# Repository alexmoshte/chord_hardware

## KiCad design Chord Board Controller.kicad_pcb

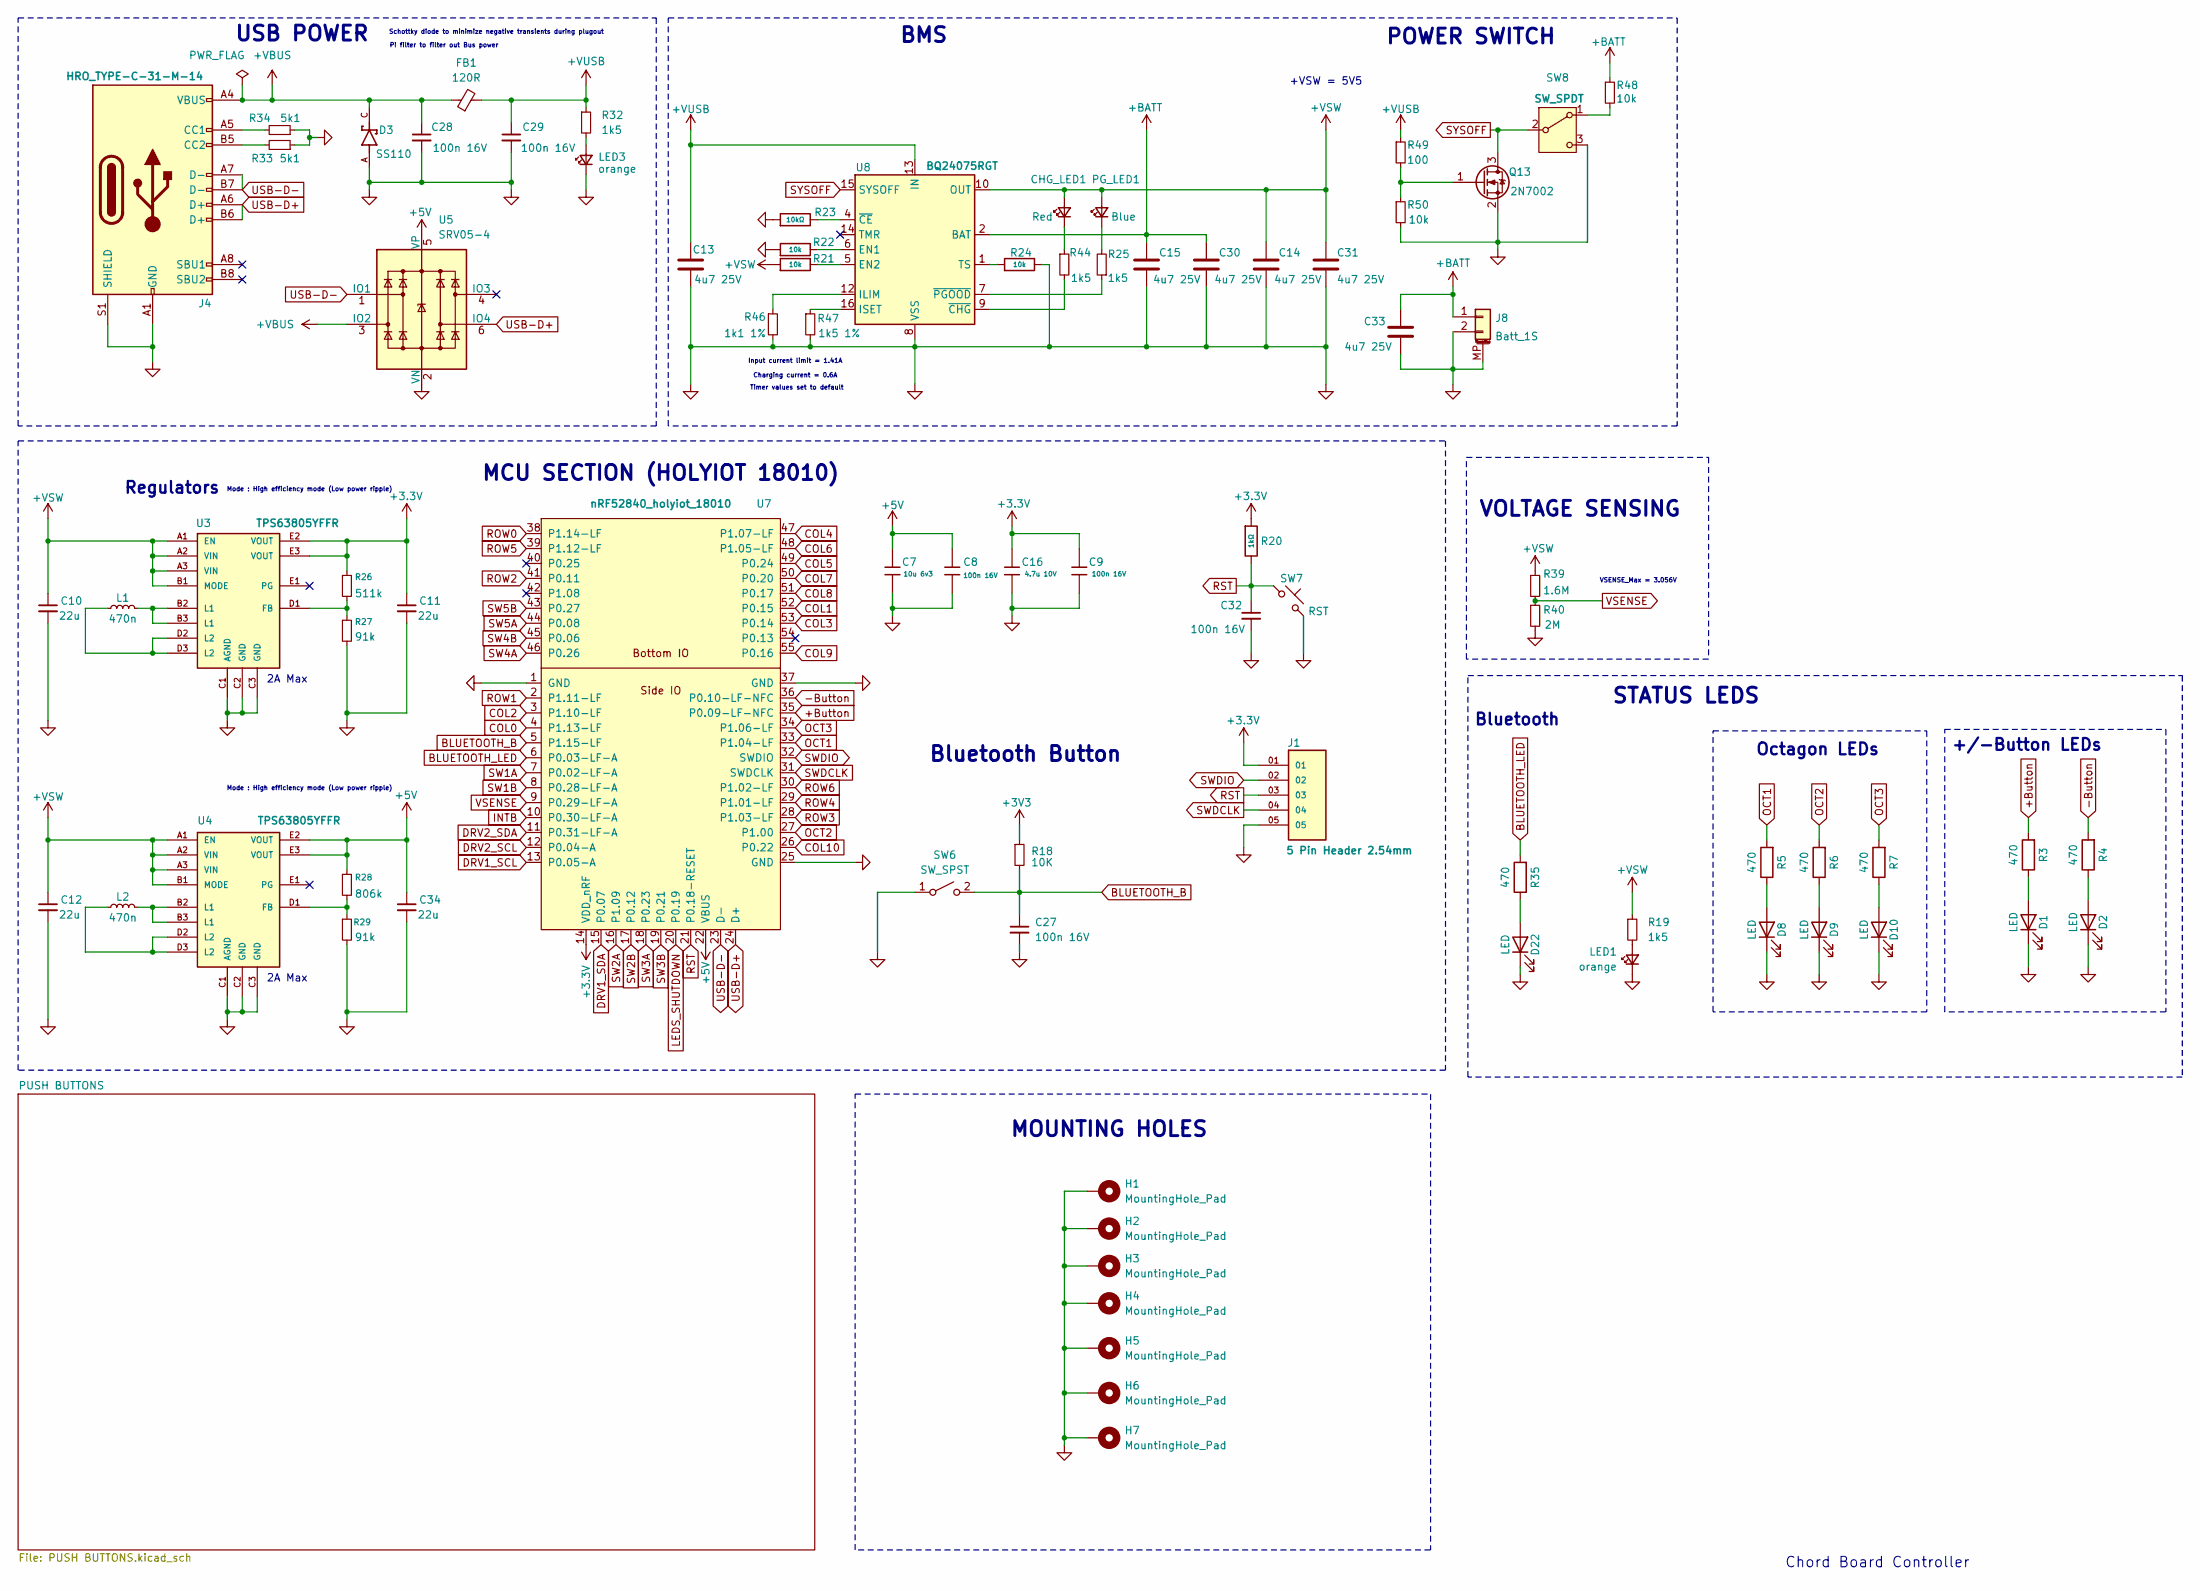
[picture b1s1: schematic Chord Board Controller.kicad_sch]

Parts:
C7: 10u 6v3; C_0402; Voltage Rated 6.3V; Tolerance ±20%; Part CL05A106MQ5NUNC; LCSC C15525
C8, C9: 100n 16V; C_0402; Voltage Rated 16V; Tolerance ±10%; Part CL05B104KO5NNNC; LCSC C1525
C10, C11, C12, C34: 22u; C_0603
C13, C14, C15, C30, C31, C33: 4u7 25V; C_0603
C16: 4.7u 10V; C_0402; Voltage Rated 10V; Tolerance ±20%; Part CL05A475MP5NRNC; LCSC C23733
C27, C32: 100n 16V; C_0402; Manufacturer Part # GCM155R71H104KE02J; LCSC C2649549
C28: 100n 16V; C_0603
C29: 100n 16V; R_0603
CHG_LED1: Red; LED_D1.8mm_W1.8mm_H2.4mm_Horizontal_O6.35mm_Z8.2mm
D1, D2, D8, D9, D10: LED; LED_0603_1608Metric
D3: SS110; DIOM4325X250N; PARTREV O2102
D22: LED; LED_D1.8mm_W1.8mm_H2.4mm_Horizontal_O6.35mm_Z8.2mm
FB1: 120R; FB_0603
H1, H2, H3, H4, H5, H6, H7: MountingHole_Pad; MountingHole_2.2mm_M2; MFR.Part # DNP; JLCPCB part# DNP
J1: 5 Pin Header 2.54mm; PARTREV R
J4: HRO_TYPE-C-31-M-14; USB_C_Receptacle_HRO_TYPE-C-31-M-14; MFR.Part # TYPE-C-31-M-12; JLCPCB part# C165948
J8: Batt_1S; JST_PH_S2B-PH-K_1x02_P2.00mm_Horizontal; LCSC C505023
L1, L2: 470n; L_0402
LED1, LED3: orange; LED_D1.8mm_W1.8mm_H2.4mm_Horizontal_O6.35mm_Z8.2mm
PG_LED1: Blue; LED_0603
Q13: 2N7002; SOT-23
R3, R4, R5, R6, R7: 470; R_0402
R18: 10K; R_0402; Manufacturer Part # CRCW040210K0FKED; LCSC C71617
R19, R32: 1k5; R_0402; MFR.Part # 0402WGF1501TCE; JLCPCB part# C25867
R20: 1kΩ; R_0402; Overload Voltage (Max) 50V; Tolerance ±1%; Part 0402WGF1001TCE; LCSC C11702
R21, R22, R24: 10k; R_0402; Overload Voltage (Max) 50V; Tolerance ±1%; Part 0402WGF1002TCE; LCSC C25744
R23: 10kΩ; R_0402; Overload Voltage (Max) 50V; Tolerance ±1%; Part 0402WGF1002TCE; LCSC C25744
R25, R44: 1k5; R_0603
R26: 511k; R_0603
R27, R29: 91k; R_0603
R28: 806k; R_0603
R33, R34: 5k1; R_0402; MFR.Part # 0402WGF5101TCE; JLCPCB part# C25905
R35: 470; R_0603
R39: 1.6M; R_0402; MFR.Part # 0402WGF8063TCE; JLCPCB part# C29263
R40: 2M; R_0402; MFR.Part # 0402WGF2004TCE; JLCPCB part# C11512
R46: 1k1 1%; R_0603
R47: 1k5 1%; R_0603
R48, R50: 10k; R_0603
R49: 100; R_0603
SW6: SW_SPST; SW_Tactile_SPST_Angled_PTS645Vx31-2LFS; Manufacturer Part # DTSA-61K-V; LCSC C483771
SW7: RST; SW_SPST_SKQG_WithStem; MFR.Part # FRC0402F1101TS; JLCPCB part# C2909306
SW8: SW_SPDT; SW_MSK12C02-HB
U3, U4: TPS63805YFFR; BGA15N40P5X3_225X134X62N; PARTREV A
U5: SRV05-4; SOT-23-6; MFR.Part # SRV05-4-P-T7; JLCPCB part# C179173
U7: nRF52840_holyiot_18010
U8: BQ24075RGT; VQFN-16-1EP_3x3mm_P0.5mm_EP1.6x1.6mm

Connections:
+3.3V: C9.1, C11.1, C16.1, J1.01, R20.1, R26.1, U3.E2 (VOUT), U3.E3 (VOUT), U7.14 (VDD_nRF); also elsewhere on the board
+3V3: R18.1
+5V: C7.1, C8.1, C34.1, R28.1, U4.E2 (VOUT), U4.E3 (VOUT), U5.5 (VP), U7.22 (VBUS)
+BATT: C15.1, C30.1, C33.1, J8.1, R48.1, U8.2 (BAT), U8.3 (BAT)
+Button: R3.2, U7.35 (P0.09-LF-NFC)
+VBUS: C28.1, D3.C, FB1.1, J4.A4 (VBUS), J4.A9 (VBUS), J4.B4 (VBUS), J4.B9 (VBUS), U5.3 (IO2)
+VSW: C10.1, C12.1, C14.1, C31.1, CHG_LED1.2 (A), PG_LED1.2 (A), R19.1, R21.1, R39.1, U3.A1 (EN), U3.A2 (VIN), U3.A3 (VIN), U3.B1 (MODE), U4.A1 (EN), U4.A2 (VIN), U4.A3 (VIN), U4.B1 (MODE), U8.10 (OUT), U8.11 (OUT); also elsewhere on the board
+VUSB: C13.1, C29.1, FB1.2, R32.1, R49.1, U8.13 (IN)
-Button: R4.2, U7.36 (P0.10-LF-NFC)
BLUETOOTH_B: C27.1, R18.2, SW6.2 (B), U7.5 (P1.15-LF)
BLUETOOTH_LED: R35.2, U7.6 (P0.03-LF-A)
COL0: U7.4 (P1.13-LF); also elsewhere on the board
COL1: U7.52 (P0.15); also elsewhere on the board
COL2: U7.3 (P1.10-LF); also elsewhere on the board
COL3: U7.53 (P0.14); also elsewhere on the board
COL4: U7.47 (P1.07-LF); also elsewhere on the board
COL5: U7.49 (P0.24); also elsewhere on the board
COL6: U7.48 (P1.05-LF); also elsewhere on the board
COL7: U7.50 (P0.20); also elsewhere on the board
COL8: U7.51 (P0.17); also elsewhere on the board
COL9: U7.55 (P0.16); also elsewhere on the board
COL10: U7.26 (P0.22); also elsewhere on the board
DRV1_SCL: U7.13 (P0.05-A); also elsewhere on the board
DRV1_SDA: U7.15 (P0.07); also elsewhere on the board
DRV2_SCL: U7.12 (P0.04-A); also elsewhere on the board
DRV2_SDA: U7.11 (P0.31-LF-A); also elsewhere on the board
GND: C7.2, C8.2, C9.2, C10.2, C11.2, C12.2, C13.2, C14.2, C15.2, C16.2, C27.2, C28.2, C29.2, C30.2, C31.2, C32.2, C33.2, C34.2, D1.1 (K), D2.1 (K), D3.A, D8.1 (K), D9.1 (K), D10.1 (K), D22.1 (K), H1.1, H2.1, H3.1, H4.1, H5.1, H6.1, H7.1, J1.05, J4.A1 (GND), J4.A12 (GND), J4.B1 (GND), J4.B12 (GND), J4.S1 (SHIELD), J8.2, J8.MP (MountPin), LED1.1 (K), LED3.1 (K), Q13.2 (S), R22.1, R23.1, R24.2, R27.2, R29.2, R33.1, R34.1, R40.2, R46.2, R47.2, R50.2, SW6.1 (A), SW7.2, SW8.3 (C), U3.C1 (AGND), U3.C2 (GND), U3.C3 (GND), U4.C1 (AGND), U4.C2 (GND), U4.C3 (GND), U5.2 (VN), U7.1 (GND), U7.25 (GND), U7.37 (GND), U8.8 (VSS), U8.17 (VSS); also elsewhere on the board
INTB: U7.10 (P0.30-LF-A); also elsewhere on the board
LEDS_SHUTDOWN: U7.20 (P0.19); also elsewhere on the board
unnamed: CHG_LED1.1 (K), R44.1
unnamed: D1.2 (A), R3.1
unnamed: D2.2 (A), R4.1
unnamed: D8.2 (A), R5.1
unnamed: D9.2 (A), R6.1
unnamed: D10.2 (A), R7.1
unnamed: D22.2 (A), R35.1
unnamed: J4.A5 (CC1), R34.2
unnamed: J4.B5 (CC2), R33.2
unnamed: L1.1, U3.D2 (L2), U3.D3 (L2)
unnamed: L1.2, U3.B2 (L1), U3.B3 (L1)
unnamed: L2.1, U4.D2 (L2), U4.D3 (L2)
unnamed: L2.2, U4.B2 (L1), U4.B3 (L1)
unnamed: LED1.2 (A), R19.2
unnamed: LED3.2 (A), R32.2
unnamed: PG_LED1.1 (K), R25.2
unnamed: Q13.1 (G), R49.2, R50.1
unnamed: R48.2, SW8.1 (A)
unnamed: R26.2, R27.1, U3.D1 (FB)
unnamed: R28.2, R29.1, U4.D1 (FB)
unnamed: R22.2, U8.6 (EN1)
unnamed: R21.2, U8.5 (EN2)
unnamed: R46.1, U8.12 (ILIM)
unnamed: R47.1, U8.16 (ISET)
unnamed: R24.1, U8.1 (TS)
unnamed: R23.2, U8.4 (~CE)
unnamed: R44.2, U8.9 (~CHG)
unnamed: R25.1, U8.7 (~PGOOD)
OCT1: R5.2, U7.33 (P1.04-LF)
OCT2: R6.2, U7.27 (P1.00)
OCT3: R7.2, U7.34 (P1.06-LF)
ROW0: U7.38 (P1.14-LF); also elsewhere on the board
ROW1: U7.2 (P1.11-LF); also elsewhere on the board
ROW2: U7.41 (P0.11); also elsewhere on the board
ROW3: U7.28 (P1.03-LF); also elsewhere on the board
ROW4: U7.29 (P1.01-LF); also elsewhere on the board
ROW5: U7.39 (P1.12-LF); also elsewhere on the board
ROW6: U7.30 (P1.02-LF); also elsewhere on the board
RST: C32.1, J1.03, R20.2, SW7.1, U7.21 (P0.18-RESET)
SW1A: U7.7 (P0.02-LF-A); also elsewhere on the board
SW1B: U7.8 (P0.28-LF-A); also elsewhere on the board
SW2A: U7.16 (P1.09); also elsewhere on the board
SW2B: U7.17 (P0.12); also elsewhere on the board
SW3A: U7.18 (P0.23); also elsewhere on the board
SW3B: U7.19 (P0.21); also elsewhere on the board
SW4A: U7.46 (P0.26); also elsewhere on the board
SW4B: U7.45 (P0.06); also elsewhere on the board
SW5A: U7.44 (P0.08); also elsewhere on the board
SW5B: U7.43 (P0.27); also elsewhere on the board
SWDCLK: J1.04, U7.31 (SWDCLK)
SWDIO: J1.02, U7.32 (SWDIO)
SYSOFF: Q13.3 (D), SW8.2 (B), U8.15 (SYSOFF)
USB-D+: J4.A6 (D+), J4.B6 (D+), U5.6 (IO4), U7.24 (D+)
USB-D-: J4.A7 (D-), J4.B7 (D-), U5.1 (IO1), U7.23 (D-)
VSENSE: R39.2, R40.1, U7.9 (P0.29-LF-A)

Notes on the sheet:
USB POWER
+/-Button LEDs
2A Max
POWER SWITCH
MOUNTING HOLES
Regulators
Octagon LEDs
Timer values set to default
MCU SECTION (HOLYIOT 18010)
Bluetooth Button
VOLTAGE SENSING
Mode : High efficiency mode (Low power ripple)
Chord Board Controller
STATUS LEDS
Pi filter to filter out Bus power
Bluetooth
Input current limit = 1.41A Charging current = 0.6A
+VSW = 5V5
Schottky diode to minimize negative transients during plugout
VSENSE_Max = 3.056V
BMS
